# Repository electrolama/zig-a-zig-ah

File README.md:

# zig-a-zig-ah

zig-a-zig-ah! (zzh, for short) is little USB-stick form factor dev board for multiprotocol RF tinkering. It utilises the TI CC2652R multi-standard wireless MCU and a USB-UART chip with a few more goodies.

Details at [electrolama.com/p/zzh](https://electrolama.com/projects/zig-a-zig-ah/).

Pre-assembled boards for sale [on our Tindie store](https://www.tindie.com/stores/electrolama/).

**Need help with your Tindie purchase?** Please send an email to support@electrolama.com. Github issues are not the right place for customer support and we do not monitor them.

zzh is designed by Electrolama / Omer Kilic and licensed under the [Solderpad Hardware License 2.0](https://solderpad.org/licenses/SHL-2.0/).

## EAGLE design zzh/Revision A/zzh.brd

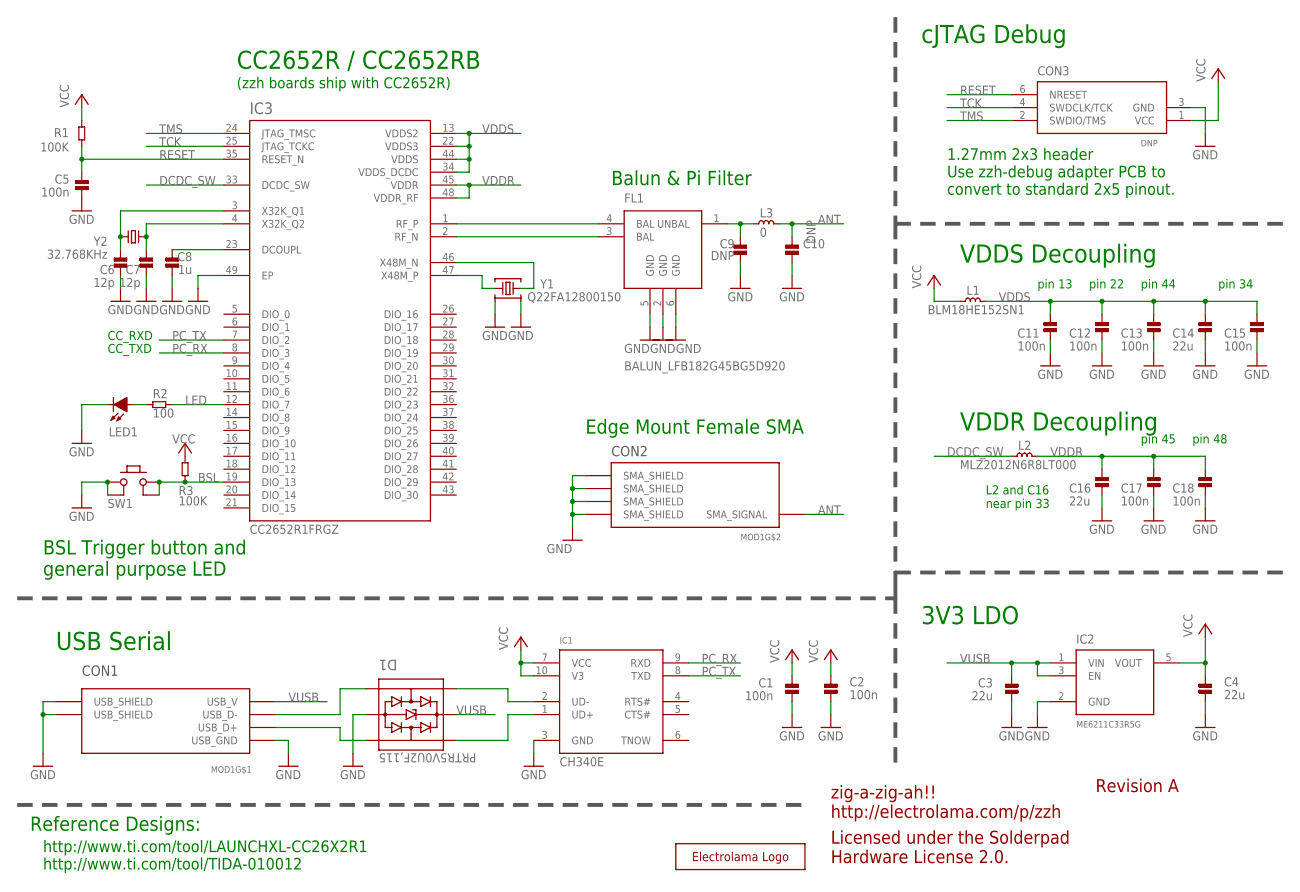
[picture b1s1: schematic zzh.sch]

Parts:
C1, C2, C5, C11, C12, C13, C15, C17, C18: 100n; _PKG_C_0402
C3, C4, C14, C16: 22u; _PKG_C_0805
C6, C7: 12p; _PKG_C_0402
C8: 1u; _PKG_C_0402
C9, C10: DNP; _PKG_C_0402
CON3: DNP; DEBUG_CORTEX_5PIN
D1: PRTR5V0U2F,115; _PKG_SOT886_JEDEC-MO-252
FL1: BALUN_LFB182G45BG5D920; LFB182G45BG5D920
IC1: CH340E; _PKG_MSOP10_TI-DGS10
IC2: ME6211C33R5G; SOT65P212X110-5N
IC3: CC2652R1FRGZ; QFN50P700X700X100-49N
L1: BLM18HE152SN1; _PKG_L_0603
L2: MLZ2012N6R8LT000; _PKG_C_0805
L3: 0; _PKG_L_0402
LED1: LED-0603; _PKG_LED_0603
MOD1: ZZH_MODULE
R1, R3: 100K; _PKG_C_0402
R2: 100; _PKG_C_0402
SW1: K2-1177SW-D4DW-06
U$5: LOGO-ELECTROLAMA; ELECTROLAMA
Y1: Q22FA12800150; XTAL-4P-2016
Y2: 32.768KHz; XTAL-2P-3215

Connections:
ANT: C10.2, L3.2, MOD1.SMA_SIGNAL
BSL: IC3.19 (DIO_13), R3.2, SW1.3 (2_1), SW1.4 (2_2)
DCDC_SW: IC3.33 (DCDC_SW), L2.1
DCOUPL: C8.2, IC3.23 (DCOUPL)
GND: C1.1, C2.1, C3.2, C4.2, C5.1, C6.1, C7.1, C8.1, C9.1, C10.1, C11.2, C12.2, C13.2, C14.2, C15.2, C16.2, C17.2, C18.2, CON3.3 (GND), D1.2, FL1.2 (GND), FL1.5 (GND), FL1.6 (GND), IC1.3 (GND), IC2.2 (GND), IC3.49 (EP), LED1.C, MOD1.SMA_SHIELD_1 (SMA_SHIELD), MOD1.SMA_SHIELD_2 (SMA_SHIELD), MOD1.SMA_SHIELD_3 (SMA_SHIELD), MOD1.SMA_SHIELD_4 (SMA_SHIELD), MOD1.USB_GND, MOD1.USB_SHIELD_1 (USB_SHIELD), MOD1.USB_SHIELD_2 (USB_SHIELD), SW1.1 (1_1), SW1.2 (1_2), Y1.2, Y1.4
LED: IC3.12 (DIO_7), R2.1
unnamed: LED1.A, R2.2
PC_RX: IC1.9 (RXD), IC3.8 (DIO_3)
PC_TX: IC1.8 (TXD), IC3.7 (DIO_2)
RESET: C5.2, CON3.6 (NRESET), IC3.35 (RESET_N), R1.1
RF_N: FL1.3 (BAL), IC3.2 (RF_N)
RF_P: FL1.4 (BAL), IC3.1 (RF_P)
TCK: CON3.4 (SWDCLK/TCK), IC3.25 (JTAG_TCKC)
TMS: CON3.2 (SWDIO/TMS), IC3.24 (JTAG_TMSC)
UD+: D1.6, IC1.1 (UD+)
UD-: D1.4, IC1.2 (UD-)
UNBAL: C9.2, FL1.1 (UNBAL), L3.1
USB_D+: D1.1, MOD1.USB_D+
USB_D-: D1.3, MOD1.USB_D-
VCC: C1.2, C2.2, C4.1, CON3.1 (VCC), IC1.7 (VCC), IC1.10 (V3), IC2.5 (VOUT), L1.1, R1.2, R3.1
VDDR: C16.1, C17.1, C18.1, IC3.45 (VDDR), IC3.48 (VDDR_RF), L2.2
VDDS: C11.1, C12.1, C13.1, C14.1, C15.1, IC3.13 (VDDS2), IC3.22 (VDDS3), IC3.34 (VDDS_DCDC), IC3.44 (VDDS), L1.2
VUSB: C3.1, D1.5, IC2.1 (VIN), IC2.3 (EN), MOD1.USB_V
X32K_Q1: C6.2, IC3.3 (X32K_Q1), Y2.1
X32K_Q2: C7.2, IC3.4 (X32K_Q2), Y2.2
X48M_N: IC3.46 (X48M_N), Y1.3
X48M_P: IC3.47 (X48M_P), Y1.1

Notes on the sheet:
VDDS Decoupling
pin 13
pin 22
pin 44
pin 34
pin 45
pin 48
VDDR Decoupling
L2 and C16 near pin 33
zig-a-zig-ah!! http://electrolama.com/p/zzh
Revision A
CC_RXD
CC_TXD
cJTAG Debug
3V3 LDO
USB Serial
CC2652R / CC2652RB
Balun & Pi Filter
BSL Trigger button and general purpose LED
Reference Designs:
http://www.ti.com/tool/LAUNCHXL-CC26X2R1 http://www.ti.com/tool/TIDA-010012
Licensed under the Solderpad Hardware License 2.0.
1.27mm 2x3 header Use zzh-debug adapter PCB to convert to standard 2x5 pinout.
CON2
CON1
(zzh boards ship with CC2652R)
Edge Mount Female SMA

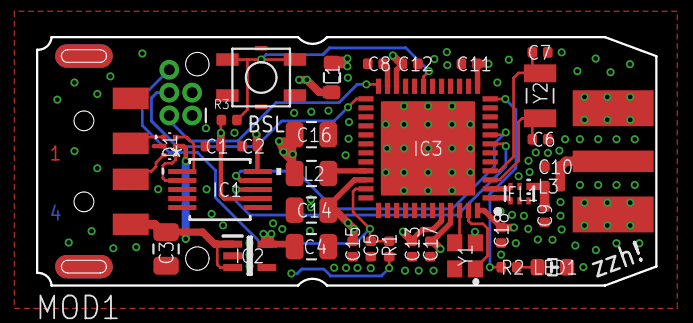
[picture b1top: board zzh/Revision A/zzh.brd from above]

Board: 4 copper layers, 34.4 x 13.8 mm, 36 parts (1 on the bottom side), 27 nets.

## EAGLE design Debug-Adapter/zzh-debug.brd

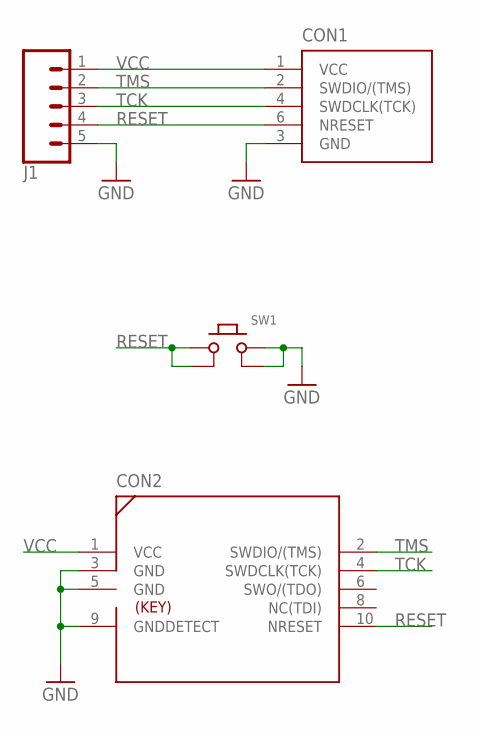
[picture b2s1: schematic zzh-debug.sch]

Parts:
CON1: DEBUG_CORTEX-SWD-5PIN-FEMALE6; SHENZHEN_2X3_1.27MM_TH_FEMALE
CON2: DEBUG_CORTEX-SWD-TH; SHENZHEN_2X5_1.27MM_TH_MALE_SHROUD
J1: CONN_05LOCK_LONGPADS; 1X05_LOCK_LONGPADS
SW1: PUSHBUTTON-K2-1177SW-D4DW-06; K2-1177SW-D4DW-06

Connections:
GND: CON1.3 (GND), CON2.3 (GND), CON2.5 (GND), CON2.9 (GNDDETECT), J1.5, SW1.3 (2_1), SW1.4 (2_2)
RESET: CON1.6 (NRESET), CON2.10 (NRESET), J1.4, SW1.1 (1_1), SW1.2 (1_2)
TCK: CON1.4 (SWDCLK(TCK)), CON2.4 (SWDCLK(TCK)), J1.3
TMS: CON1.2 (SWDIO/(TMS)), CON2.2 (SWDIO/(TMS)), J1.2
VCC: CON1.1 (VCC), CON2.1 (VCC), J1.1

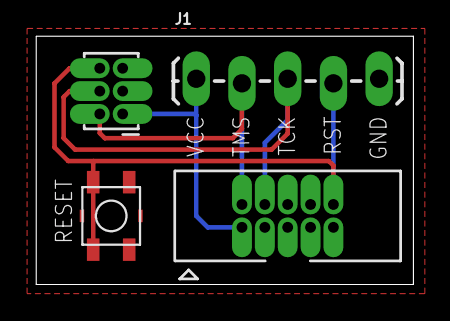
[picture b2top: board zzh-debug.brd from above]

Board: 2 copper layers, 21.0 x 13.8 mm, 4 parts (0 on the bottom side), 5 nets.

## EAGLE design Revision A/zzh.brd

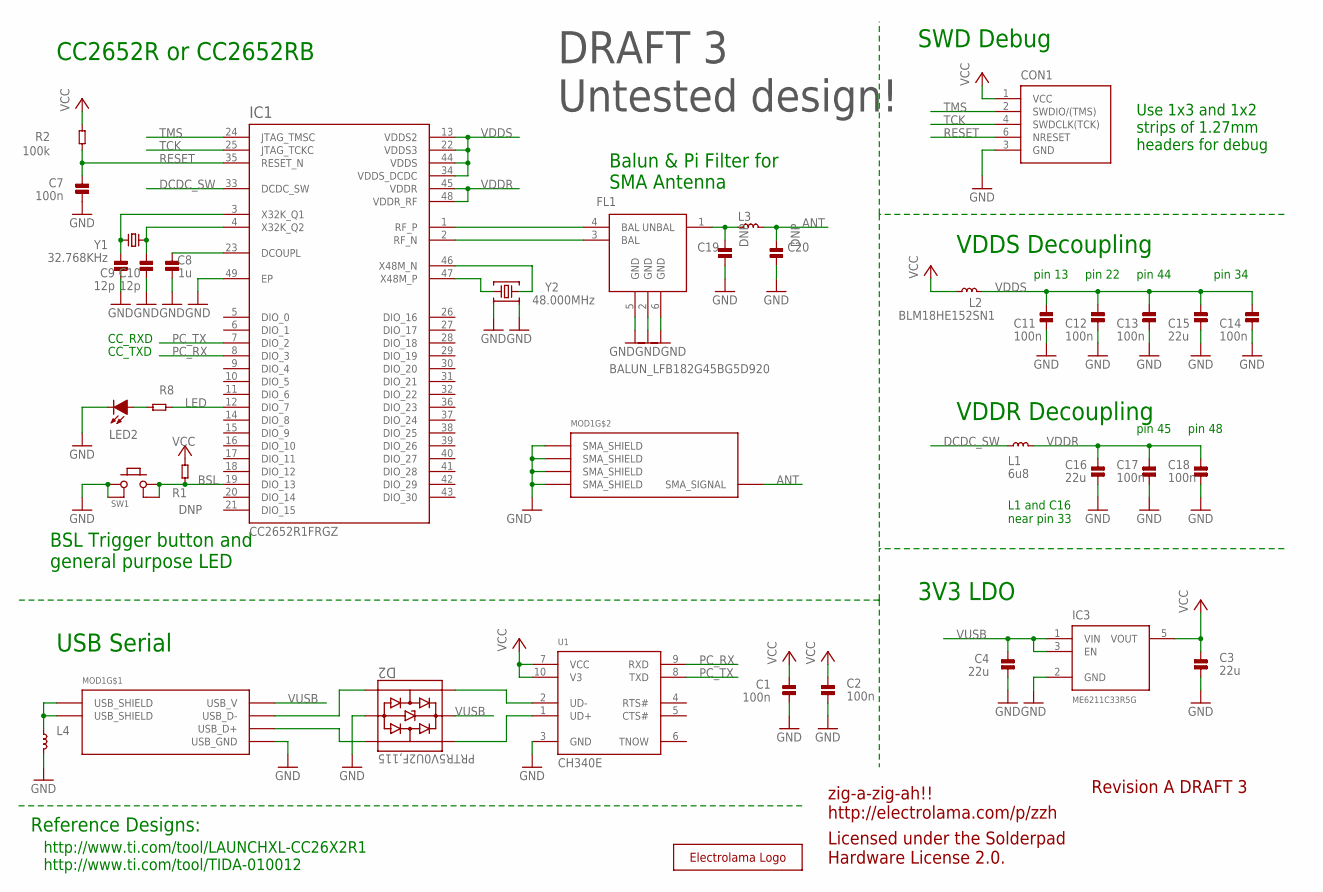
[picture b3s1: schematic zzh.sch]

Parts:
C1, C2, C7, C11, C12, C13, C14, C17, C18: 100n; _PKG_C_0402
C3, C4, C15, C16: 22u; _PKG_C_0805
C8: 1u; _PKG_C_0402
C9, C10: 12p; _PKG_C_0402
C19, C20: DNP; _PKG_C_0402
CON1: DEBUG_CORTEX-SWD-5PIN-CUT5; DEBUG_CORTEX_5PIN
D2: PRTR5V0U2F,115; _PKG_SOT886_JEDEC-MO-252
FL1: BALUN_LFB182G45BG5D920; LFB182G45BG5D920
IC1: CC2652R1FRGZ; QFN50P700X700X100-49N
IC3: ME6211C33R5G; SOT65P212X110-5N
L1: 6u8; _PKG_C_0805
L2: BLM18HE152SN1; _PKG_L_0603
L3, L4: INDUCTOR-0402; _PKG_L_0402
LED2: LED-0603; _PKG_LED_0603
MOD1: ZZH_MODULE
R1: DNP; _PKG_C_0402
R2: 100k; _PKG_C_0402
R8: RES-0402; _PKG_C_0402
SW1: K2-1177SW-D4DW-06
U1: CH340E; _PKG_MSOP10_TI-DGS10
U$5: LOGO-ELECTROLAMA; ELECTROLAMA
Y1: 32.768KHz; XTAL-2P-3215
Y2: 48.000MHz; XTAL-4P-2016

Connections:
ANT: C20.2, L3.2, MOD1.SMA_SIGNAL
BSL: IC1.19 (DIO_13), R1.2, SW1.3 (2_1), SW1.4 (2_2)
DCDC_SW: IC1.33 (DCDC_SW), L1.1
DCOUPL: C8.2, IC1.23 (DCOUPL)
GND: C1.1, C2.1, C3.2, C4.2, C7.1, C8.1, C9.1, C10.1, C11.2, C12.2, C13.2, C14.2, C15.2, C16.2, C17.2, C18.2, C19.1, C20.1, CON1.3 (GND), D2.2, FL1.2 (GND), FL1.5 (GND), FL1.6 (GND), IC1.49 (EP), IC3.2 (GND), L4.2, LED2.C, MOD1.SMA_SHIELD_1 (SMA_SHIELD), MOD1.SMA_SHIELD_2 (SMA_SHIELD), MOD1.SMA_SHIELD_3 (SMA_SHIELD), MOD1.SMA_SHIELD_4 (SMA_SHIELD), MOD1.USB_GND, SW1.1 (1_1), SW1.2 (1_2), U1.3 (GND), Y2.2, Y2.4
LED: IC1.12 (DIO_7), R8.1
unnamed: L4.1, MOD1.USB_SHIELD_1 (USB_SHIELD), MOD1.USB_SHIELD_2 (USB_SHIELD)
unnamed: LED2.A, R8.2
PC_RX: IC1.8 (DIO_3), U1.9 (RXD)
PC_TX: IC1.7 (DIO_2), U1.8 (TXD)
RESET: C7.2, CON1.6 (NRESET), IC1.35 (RESET_N), R2.1
RF_N: FL1.3 (BAL), IC1.2 (RF_N)
RF_P: FL1.4 (BAL), IC1.1 (RF_P)
TCK: CON1.4 (SWDCLK(TCK)), IC1.25 (JTAG_TCKC)
TMS: CON1.2 (SWDIO/(TMS)), IC1.24 (JTAG_TMSC)
UD+: D2.6, U1.1 (UD+)
UD-: D2.4, U1.2 (UD-)
UNBAL: C19.2, FL1.1 (UNBAL), L3.1
USB_D+: D2.1, MOD1.USB_D+
USB_D-: D2.3, MOD1.USB_D-
VCC: C1.2, C2.2, C3.1, CON1.1 (VCC), IC3.5 (VOUT), L2.1, R1.1, R2.2, U1.7 (VCC), U1.10 (V3)
VDDR: C16.1, C17.1, C18.1, IC1.45 (VDDR), IC1.48 (VDDR_RF), L1.2
VDDS: C11.1, C12.1, C13.1, C14.1, C15.1, IC1.13 (VDDS2), IC1.22 (VDDS3), IC1.34 (VDDS_DCDC), IC1.44 (VDDS), L2.2
VUSB: C4.1, D2.5, IC3.1 (VIN), IC3.3 (EN), MOD1.USB_V
X32K_Q1: C9.2, IC1.3 (X32K_Q1), Y1.1
X32K_Q2: C10.2, IC1.4 (X32K_Q2), Y1.2
X48M_N: IC1.46 (X48M_N), Y2.3
X48M_P: IC1.47 (X48M_P), Y2.1

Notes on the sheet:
VDDS Decoupling
pin 13
pin 22
pin 44
pin 34
pin 45
pin 48
VDDR Decoupling
L1 and C16 near pin 33
zig-a-zig-ah!! http://electrolama.com/p/zzh
Revision A DRAFT 3
CC_RXD
CC_TXD
SWD Debug
3V3 LDO
USB Serial
CC2652R or CC2652RB
Balun & Pi Filter for SMA Antenna
BSL Trigger button and general purpose LED
Reference Designs:
http://www.ti.com/tool/LAUNCHXL-CC26X2R1 http://www.ti.com/tool/TIDA-010012
Licensed under the Solderpad Hardware License 2.0.
Use 1x3 and 1x2 strips of 1.27mm headers for debug
DRAFT 3 Untested design!

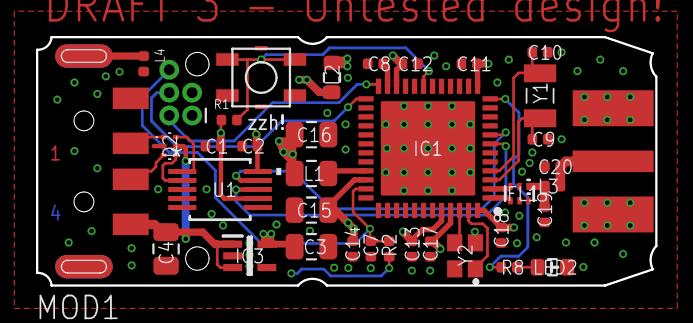
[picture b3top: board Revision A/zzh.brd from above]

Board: 4 copper layers, 34.4 x 13.8 mm, 37 parts (1 on the bottom side), 28 nets.

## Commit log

2020-01-02 add ignores
2020-02-01 Revision A, Draft 1 check-in
2020-02-01 add license
2020-02-03 Revision A, Draft 2 check-in
2020-02-09 Revision A, Draft 3 check-in
2020-02-09 debug-adapter, Revision A check-in
2020-05-10 zzh: Revision A release
2020-05-10 update README, add CHANGELOG

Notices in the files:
parts and their libraries:
SparkFun-Connectors: Licensing: Creative Commons ShareAlike 4.0 International - https://creativecommons.org/licenses/by-sa/4.0
